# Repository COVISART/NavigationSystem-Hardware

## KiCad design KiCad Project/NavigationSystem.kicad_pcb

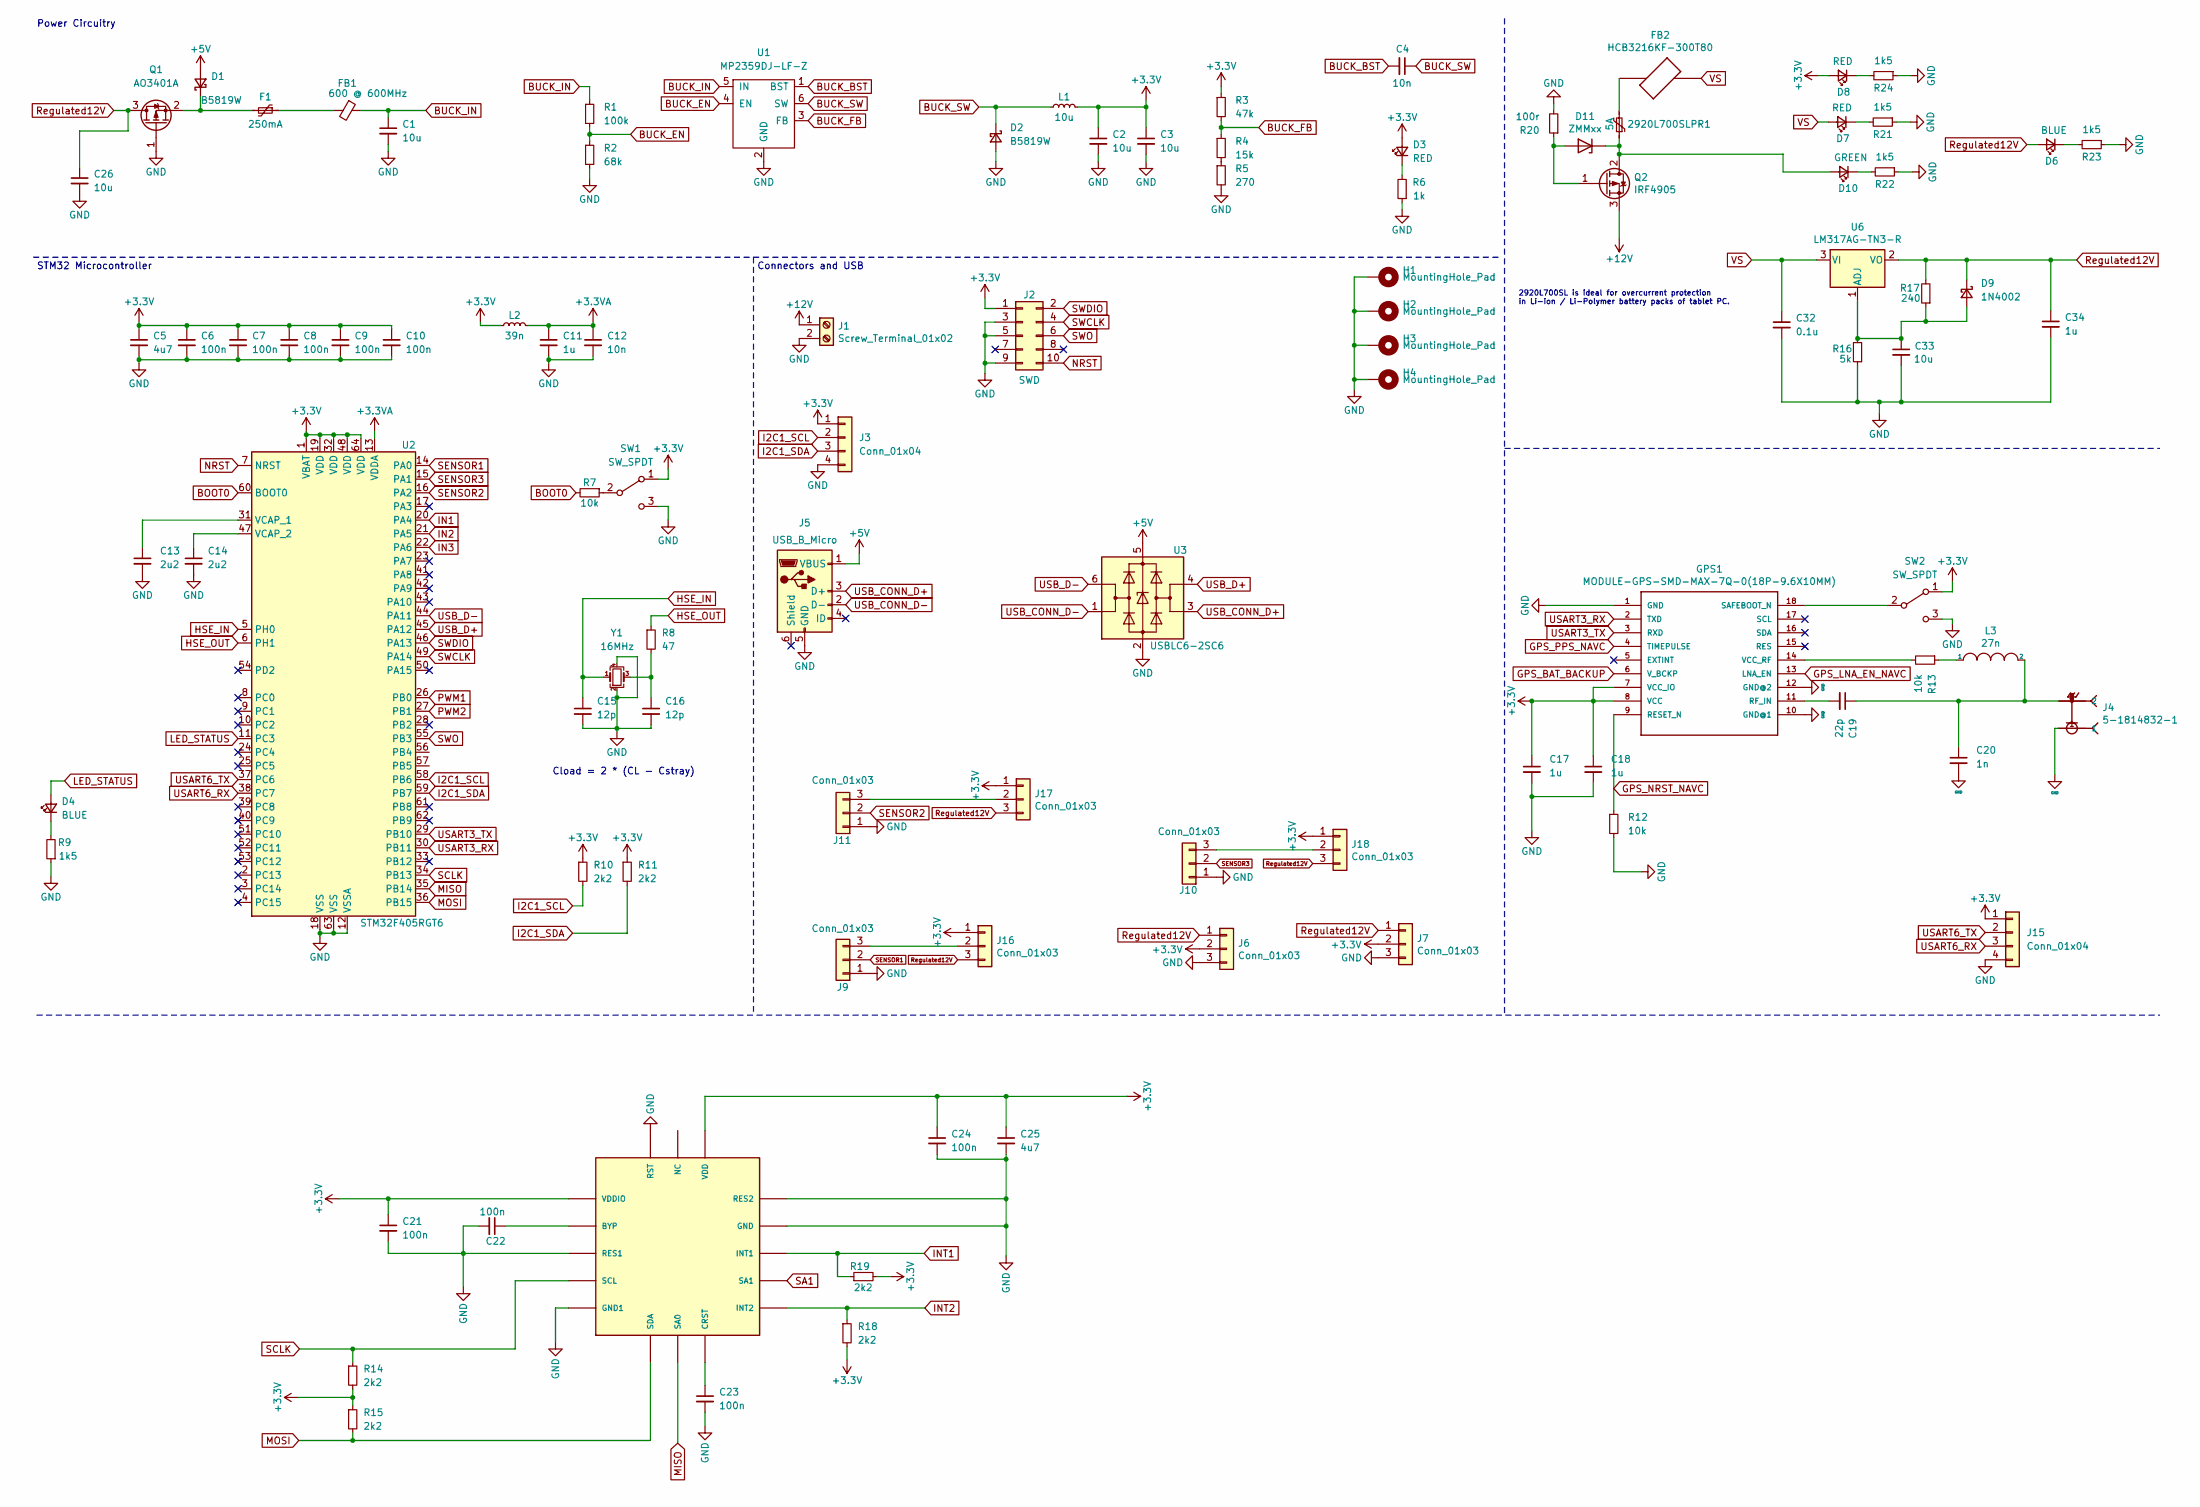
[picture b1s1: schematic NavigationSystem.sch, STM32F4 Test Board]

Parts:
2920L700SLPR1: 5A; Fuse_2920_7451Metric; LCSC Part # C207093
C1, C2, C3, C26, C33: 10u; C_1206_3216Metric; LCSC Part # C13585
C4: 10n; C_0603_1608Metric; LCSC Part # C57112
C5: 4u7; C_0603_1608Metric; LCSC Part # C19666
C6, C7, C8, C9, C10, C21, C22, C23, C24: 100n; C_0402_1005Metric; LCSC Part # C1525
C11: 1u; C_0402_1005Metric; LCSC Part # C52923
C12: 10n; C_0402_1005Metric; LCSC Part # C15195
C13, C14: 2u2; C_0603_1608Metric; LCSC Part # C23630
C15, C16: 12p; C_0402_1005Metric; LCSC Part # C1547
C17, C18: 1u; C_0603_1608Metric; LCSC Part # C23630
C19: 22p; C_0402_1005Metric; LCSC Part # C23630
C20: 1n; C_0402_1005Metric; LCSC Part # C23630
C25: 4u7; C_0402_1005Metric; LCSC Part # C1525
C32: 0.1u; C_1206_3216Metric; LCSC Part # C13585
C34: 1u; C_1206_3216Metric; LCSC Part # C13585
D1, D2: B5819W; D_SOD-123; LCSC Part # C8598
D3: RED; LED_0603_1608Metric; LCSC Part # C2286
D4, D6: BLUE; LED_0603_1608Metric; LCSC Part # C72041
D7, D8: RED; LED_0603_1608Metric; LCSC Part # C72041
D9: 1N4002; D_SOD-123; LCSC Part # C8598
D10: GREEN; LED_0603_1608Metric; LCSC Part # C72041
D11: ZMMxx; D_MiniMELF
F1: 250mA; Fuse_1206_3216Metric; LCSC Part # C369159
FB1: 600 @ 600MHz; L_0805_2012Metric; LCSC Part # C1017
FB2: HCB3216KF-300T80; C_1206_3216Metric; LCSC Part # C525677
GPS1: MODULE-GPS-SMD-MAX-7Q-0(18P-9.6X10MM); ublox_MAX
H1, H2, H3, H4: MountingHole_Pad; MountingHole_4.3mm_M4_Pad_Via
J1: Screw_Terminal_01x02; PhoenixContact_MCV_1,5_2-G-3.5_1x02_P3.50mm_Vertical
J2: SWD; PinHeader_2x05_P1.27mm_Vertical_SMD
J3, J15: Conn_01x04; Molex_PicoBlade_53048-0410_1x04_P1.25mm_Horizontal
J4: 5-1814832-1; TE_5-1814832-1
J5: USB_B_Micro; USB_MICRO_B_101181930001LF
J6, J7, J16, J17, J18: Conn_01x03; PinHeader_1x03_P1.27mm_Vertical
J9, J10, J11: Conn_01x03; FanPinHeader_1x03_P2.54mm_Vertical
L1: 10u; L_Sunlord_MWSA0518_5.4x5.2mm; LCSC Part # C139506
L2: 39n; L_0402_1005Metric; LCSC Part # C26443
L3: 27n; L_0402_1005Metric
Q1: AO3401A; SOT-23; LCSC Part # C15127
Q2: IRF4905; TO-263-2
R1: 100k; R_0603_1608Metric; LCSC Part # C25803
R2: 68k; R_0603_1608Metric; LCSC Part # C23231
R3: 47k; R_0603_1608Metric; LCSC Part # C25819
R4: 15k; R_0603_1608Metric; LCSC Part # C22809
R5: 270; R_0603_1608Metric; LCSC Part # C22966
R6: 1k; R_0603_1608Metric; LCSC Part # C21190
R7: 10k; R_0402_1005Metric; LCSC Part # C25744
R8: 47; R_0402_1005Metric; LCSC Part # C25118
R9, R21, R22, R23, R24: 1k5; R_0603_1608Metric; LCSC Part # C22843
R10, R11, R14, R15, R18, R19: 2k2; R_0402_1005Metric; LCSC Part # C25879
R12, R13: 10k; R_0603_1608Metric; LCSC Part # C22809
R16: 5k; R_0603_1608Metric; LCSC Part # C23231
R17: 240; R_0603_1608Metric; LCSC Part # C23231
R20: 100r; R_0603_1608Metric; LCSC Part # C25819
SW1, SW2: SW_SPDT; SW_SPDT_PCM12
U1: MP2359DJ-LF-Z; SOT-23-6; LCSC Part # C14259
U2: STM32F405RGT6; LQFP-64_10x10mm_P0.5mm; LCSC Part # C15742
U3: USBLC6-2SC6; SOT-23-6; LCSC Part # C7519
U4: FXOS8700CQ; FSOS8700CQ_PKG
U6: LM317AG-TN3-R; TO-252-2; LCSC Part # C75510
Y1: 16MHz; Crystal_SMD_3225-4Pin_3.2x2.5mm; LCSC Part # C13738

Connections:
+3.3VA: C11.1, C12.1, L2.2, U2.13 (VDDA)
+3V3: C2.1, C3.1, C5.1, C6.1, C7.1, C8.1, C9.1, C10.1, C17.1, C18.1, C21.1, C24.1, C25.1, D3.2 (A), D8.2 (A), GPS1.7 (VCC_IO), GPS1.8 (VCC), J2.1, J3.1, J6.2, J7.2, J15.1, J16.1, J17.1, J18.1, L1.2, L2.1, R3.1, R10.1, R11.1, R14.2, R15.1, R18.2, R19.2, SW1.1 (A), SW2.1 (A), U2.1 (VBAT), U2.19 (VDD), U2.32 (VDD), U2.48 (VDD), U2.64 (VDD), U4.P$1 (VDDIO), U4.P$14 (VDD)
+5V: D1.2 (A), J5.1 (VBUS), U3.5 (VBUS)
+12V: J1.1, Q2.3 (S)
BOOT0: R7.2, U2.60 (BOOT0)
BUCK_BST: C4.2, U1.1 (BST)
BUCK_EN: R1.2, R2.1, U1.4 (EN)
BUCK_FB: R3.2, R4.1, U1.3 (FB)
BUCK_IN: C1.1, FB1.1, R1.1, U1.5 (IN)
BUCK_SW: C4.1, D2.1 (K), L1.1, U1.6 (SW)
GND: C1.2, C2.2, C3.2, C5.2, C6.2, C7.2, C8.2, C9.2, C10.2, C11.2, C12.2, C13.2, C14.2, C15.2, C16.2, C17.2, C18.2, C20.2, C21.2, C22.2, C23.2, C24.2, C25.2, C26.2, C32.2, C33.2, C34.2, D2.2 (A), GPS1.1 (GND), GPS1.10 (GND@1), GPS1.12 (GND@2), H1.1, H2.1, H3.1, H4.1, J1.2, J2.3, J2.5, J2.9, J3.4, J4.1, J5.5 (GND), J6.3, J7.3, J9.1, J10.1, J11.1, J15.4, Q1.1 (G), R2.2, R5.2, R6.1, R9.1, R12.2, R16.1, R20.2, R21.1, R22.1, R23.1, R24.1, SW1.3 (C), SW2.3 (C), U1.2 (GND), U2.12 (VSSA), U2.18 (VSS), U2.63 (VSS), U3.2 (GND), U4.P$3 (RES1), U4.P$5 (GND1), U4.P$12 (GND), U4.P$13 (RES2), U4.P$16 (RST), Y1.2, Y1.4; also elsewhere on the board
GPS_BAT_BACKUP: GPS1.6 (V_BCKP)
GPS_LNA_EN_NAVC: GPS1.13 (LNA_EN)
GPS_NRST_NAVC: GPS1.9 (RESET_N), R12.1
GPS_PPS_NAVC: GPS1.4 (TIMEPULSE)
HSE_IN: C15.1, U2.5 (PH0), Y1.1
HSE_OUT: R8.1, U2.6 (PH1)
I2C1_SCL: J3.2, R10.2, U2.58 (PB6)
I2C1_SDA: J3.3, R11.2, U2.59 (PB7)
IN1: U2.20 (PA4)
IN2: U2.21 (PA5)
IN3: U2.22 (PA6)
INT1: R19.1, U4.P$11 (INT1)
INT2: R18.1, U4.P$9 (INT2)
LED_STATUS: D4.2 (A), U2.11 (PC3)
MISO: U2.35 (PB14), U4.P$7 (SA0)
MOSI: R15.2, U2.36 (PB15), U4.P$6 (SDA)
NRST: J2.10, U2.7 (NRST)
unnamed: 2920L700SLPR1.1, D10.2 (A), D11.1 (K), Q2.2 (D)
unnamed: 2920L700SLPR1.2, FB2.1
unnamed: C13.1, U2.31 (VCAP_1)
unnamed: C14.1, U2.47 (VCAP_2)
unnamed: C16.1, R8.2, Y1.3
unnamed: C19.1, C20.1, J4.2, J4.3 (2), J4.4 (2), J4.5 (2), L3.2
unnamed: C19.2, GPS1.11 (RF_IN)
unnamed: C22.1, U4.P$2 (BYP)
unnamed: C23.1, U4.P$8 (CRST)
unnamed: C33.1, D9.2 (A), R16.2, R17.1, U6.1 (ADJ)
unnamed: D1.1 (K), F1.2, Q1.2 (S)
unnamed: D3.1 (K), R6.2
unnamed: D4.1 (K), R9.2
unnamed: D6.1 (K), R23.2
unnamed: D7.1 (K), R21.2
unnamed: D8.1 (K), R24.2
unnamed: D10.1 (K), R22.2
unnamed: D11.2 (A), Q2.1 (G), R20.1
unnamed: F1.1, FB1.2
unnamed: GPS1.14 (VCC_RF), R13.2
unnamed: GPS1.18 (SAFEBOOT_N), SW2.2 (B)
unnamed: J10.3, J18.2
unnamed: J11.3, J17.2
unnamed: J9.3, J16.2
unnamed: L3.1, R13.1
unnamed: R4.2, R5.1
unnamed: R7.1, SW1.2 (B)
PWM1: U2.26 (PB0)
PWM2: U2.27 (PB1)
Regulated12V: C26.1, C34.1, D6.2 (A), D9.1 (K), J6.1, J7.1, J16.3, J17.3, J18.3, Q1.3 (D), R17.2, U6.2 (VO)
SA1: U4.P$10 (SA1)
SCLK: R14.1, U2.34 (PB13), U4.P$4 (SCL)
SENSOR1: J9.2, U2.14 (PA0)
SENSOR2: J11.2, U2.16 (PA2)
SENSOR3: J10.2, U2.15 (PA1)
SWCLK: J2.4, U2.49 (PA14)
SWDIO: J2.2, U2.46 (PA13)
SWO: J2.6, U2.55 (PB3)
USART3_RX: GPS1.2 (TXD), U2.30 (PB11)
USART3_TX: GPS1.3 (RXD), U2.29 (PB10)
USART6_RX: J15.3, U2.38 (PC7)
USART6_TX: J15.2, U2.37 (PC6)
USB_CONN_D+: J5.3 (D+), U3.3 (I/O2)
USB_CONN_D-: J5.2 (D-), U3.1 (I/O1)
USB_D+: U2.45 (PA12), U3.4 (I/O2)
USB_D-: U2.44 (PA11), U3.6 (I/O1)
VS: C32.1, D7.2 (A), FB2.2, U6.3 (VI)

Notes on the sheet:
Cload = 2 * (CL - Cstray)
STM32 Microcontroller
Power Circuitry
Connectors and USB
2920L700SL is ideal for overcurrent protection in Li-ion / Li-Polymer battery packs of tablet PC.

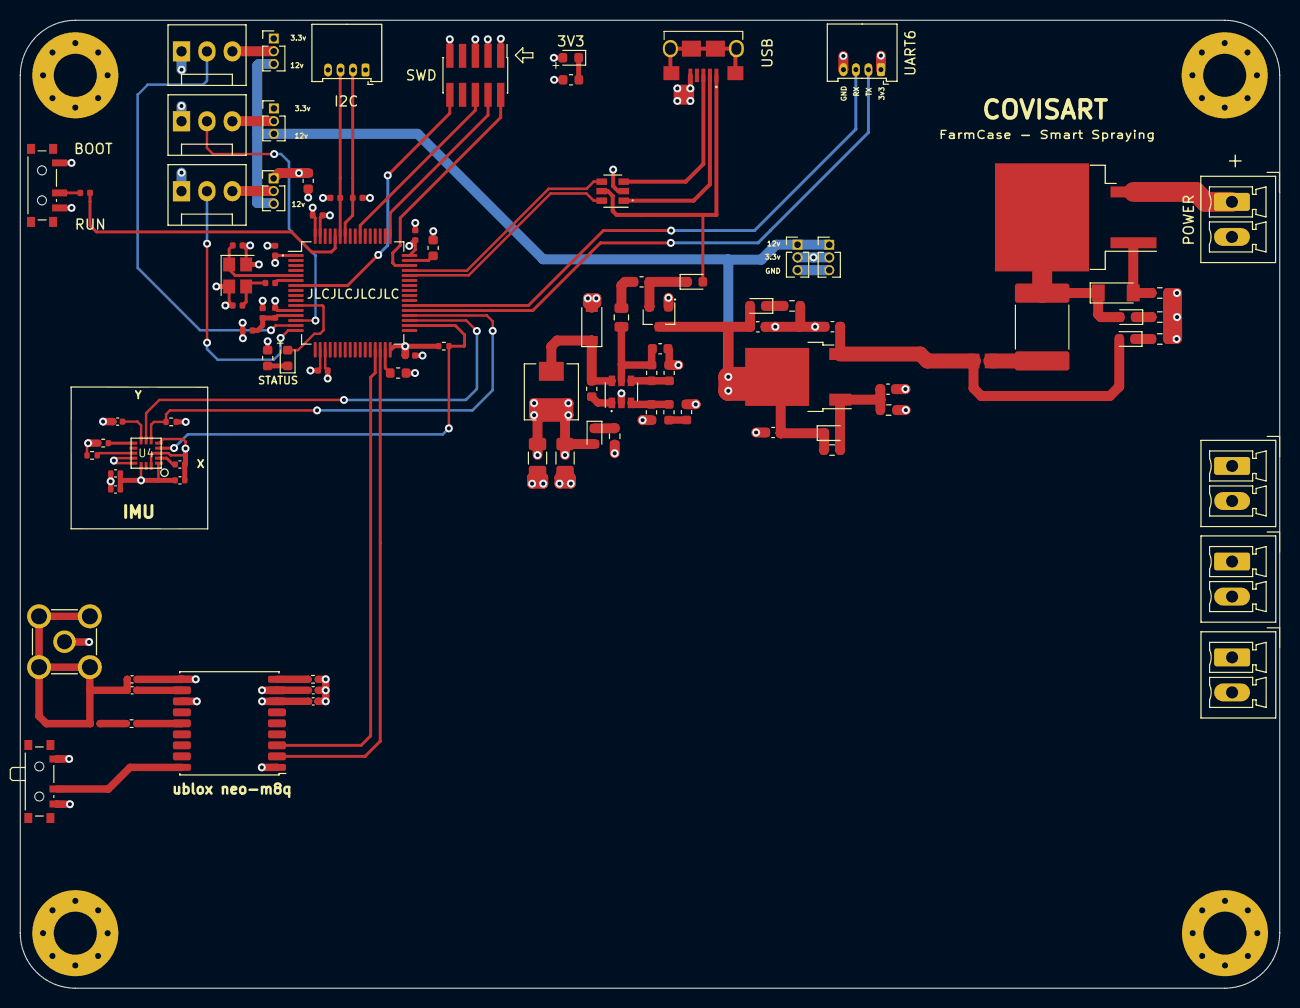
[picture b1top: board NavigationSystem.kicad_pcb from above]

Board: 4 copper layers, 125.8 x 96.7 mm, 102 parts (0 on the bottom side), 66 nets.

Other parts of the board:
J6#2, J7#2, J8: Screw_Terminal_01x02; PhoenixContact_MCV_1,5_2-G-3.5_1x02_P3.50mm_Vertical

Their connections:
GND: J6#2.2, J7#2.2, J8.2; also elsewhere on the board

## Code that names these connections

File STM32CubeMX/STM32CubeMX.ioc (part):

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Mcu.Name=STM32F405RGTx
Mcu.Package=LQFP64
Mcu.UserName=STM32F405RGTx
PA0-WKUP.Signal=ADCx_IN0
PA1.Signal=ADCx_IN1
PA10.Mode=Asynchronous
PA10.Signal=USART1_RX
PA11.Mode=Host_Only
PA11.Signal=USB_OTG_FS_DM
PA12.Mode=Host_Only
PA12.Signal=USB_OTG_FS_DP
PA13.Mode=Serial_Wire
PA13.Signal=SYS_JTMS-SWDIO
PA14.Mode=Serial_Wire
PA14.Signal=SYS_JTCK-SWCLK
PA2.Signal=ADCx_IN2
PA3.Signal=ADCx_IN3
PA4.Signal=GPIO_Output
PA5.Signal=GPIO_Output
PA6.Signal=GPIO_Output
PA7.Signal=GPIO_Output
PA9.Mode=Asynchronous
PA9.Signal=USART1_TX
PB0.Signal=S_TIM3_CH3
PB1.Signal=S_TIM3_CH4
PB10.Mode=Asynchronous
PB10.Signal=USART3_TX
PB11.Mode=Asynchronous
PB11.Signal=USART3_RX
PB6.Mode=I2C
PB6.Signal=I2C1_SCL
PB7.Mode=I2C
PB7.Signal=I2C1_SDA
PC0.Signal=GPIO_Output
PC1.Signal=GPIO_Output
PC2.Signal=GPIO_Output
PC3.Signal=GPIO_Output
PC4.Signal=GPIO_Output
PC5.Signal=GPIO_Output
PC6.Mode=Asynchronous
PC6.Signal=USART6_TX
PC7.Mode=Asynchronous
PC7.Signal=USART6_RX
PH0-OSC_IN.Mode=HSE-External-Oscillator
PH0-OSC_IN.Signal=RCC_OSC_IN
PH1-OSC_OUT.Mode=HSE-External-Oscillator
PH1-OSC_OUT.Signal=RCC_OSC_OUT
RCC.HSE_VALUE=25000000
RCC.SYSCLKFreq_VALUE=168000000
RCC.SYSCLKSource=RCC_SYSCLKSOURCE_PLLCLK
board=custom

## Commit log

2020-11-23 KiCad Project added
2020-11-28 power modules updated
    reverse polarity protection
